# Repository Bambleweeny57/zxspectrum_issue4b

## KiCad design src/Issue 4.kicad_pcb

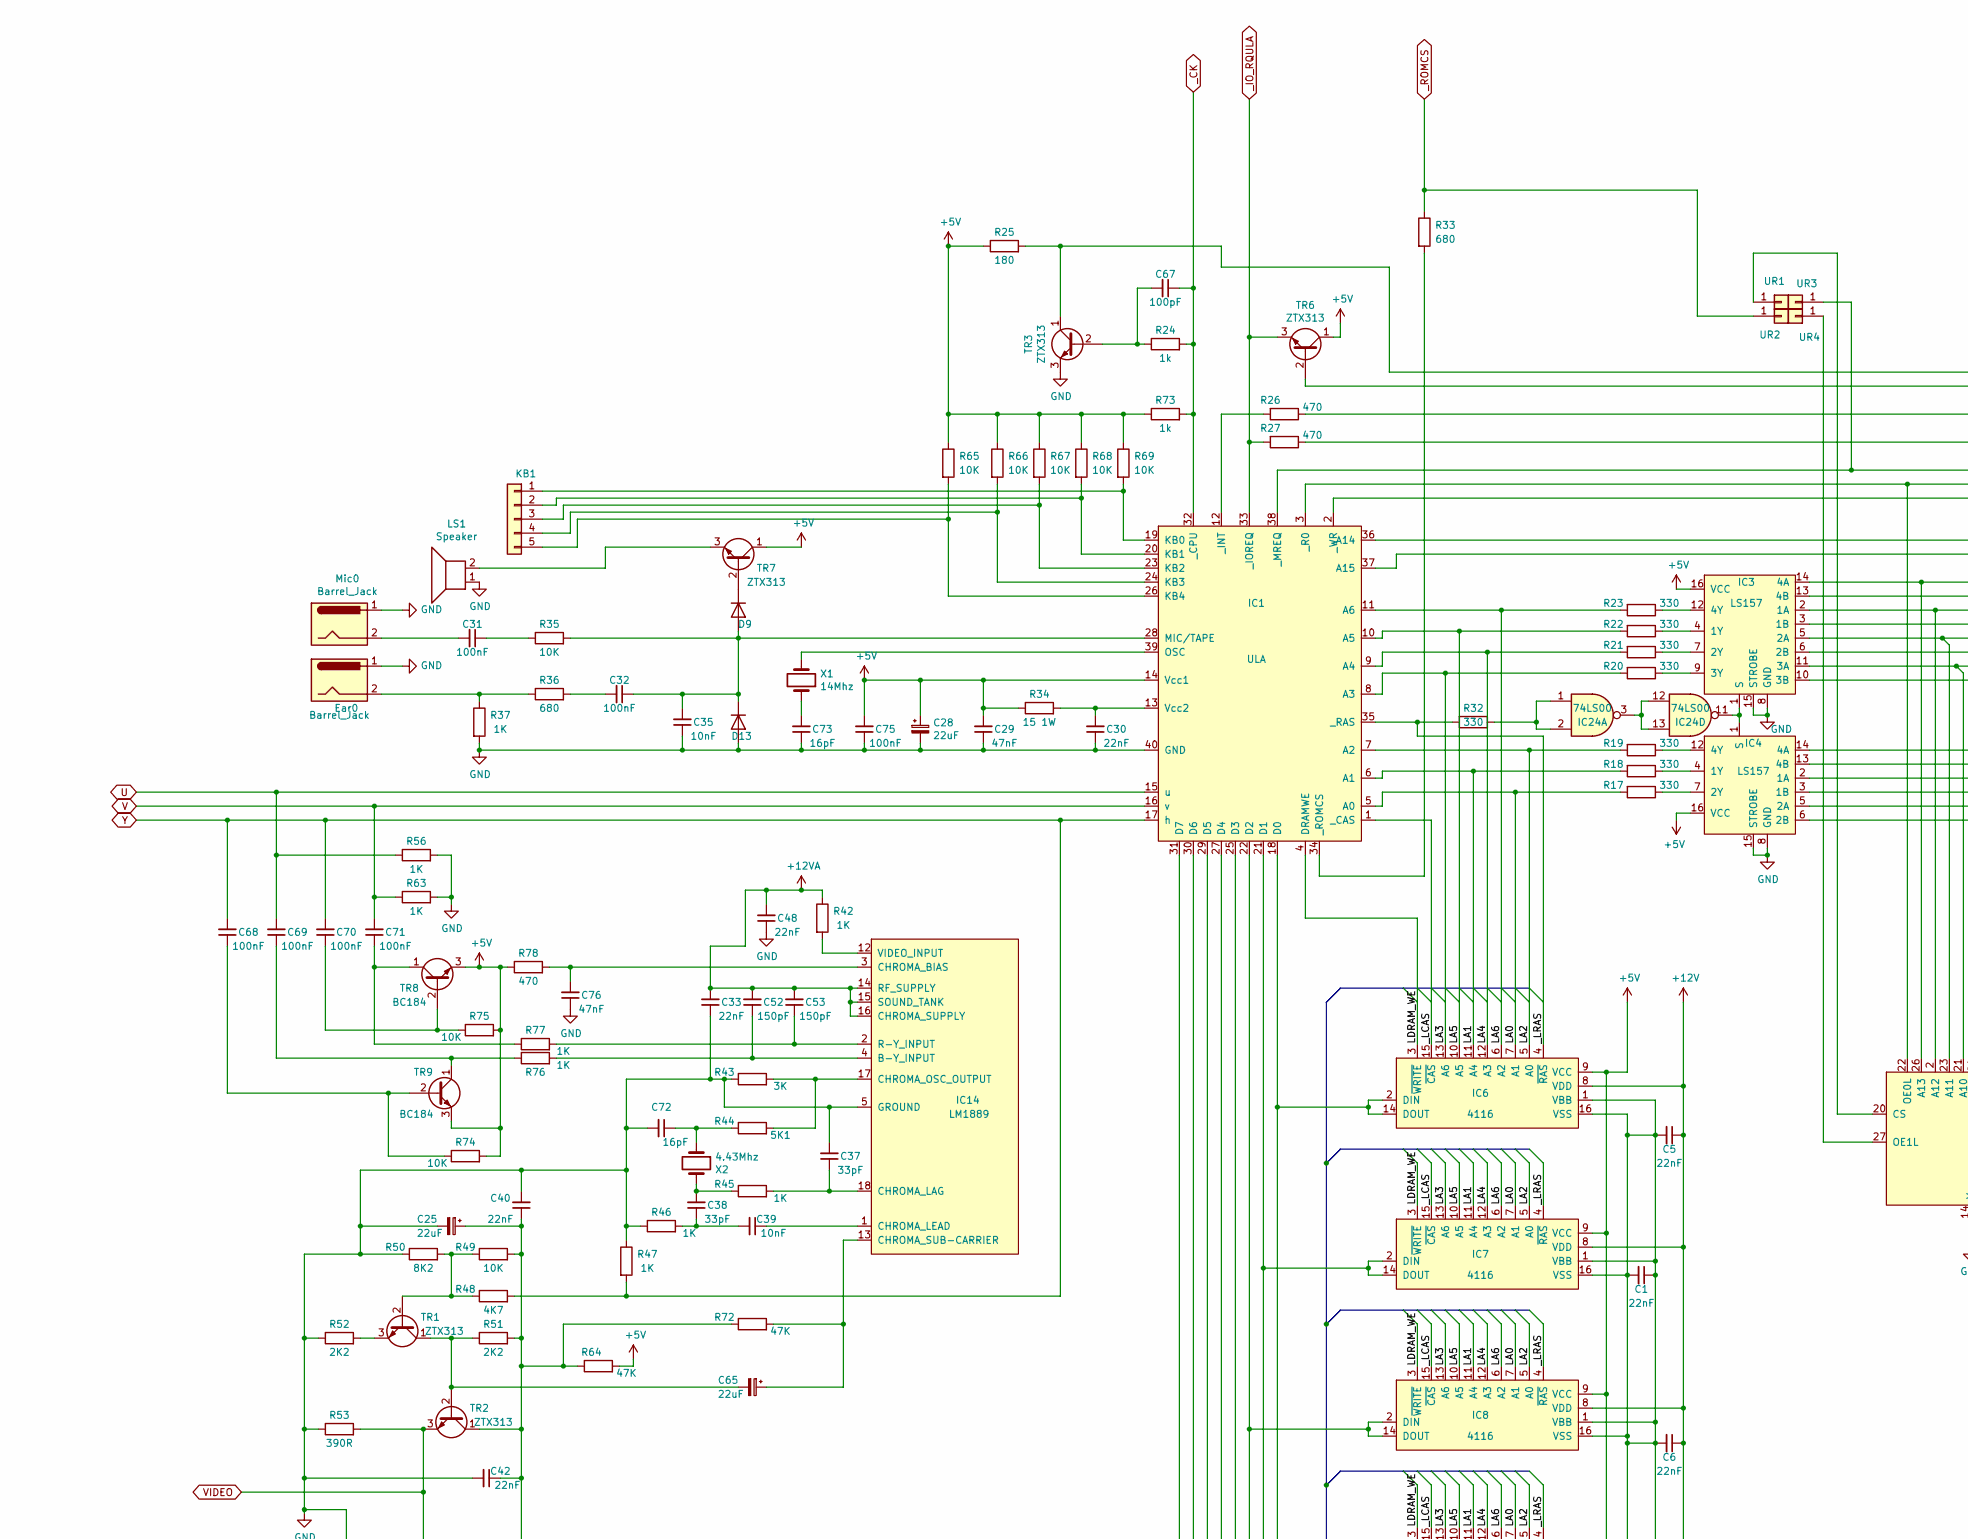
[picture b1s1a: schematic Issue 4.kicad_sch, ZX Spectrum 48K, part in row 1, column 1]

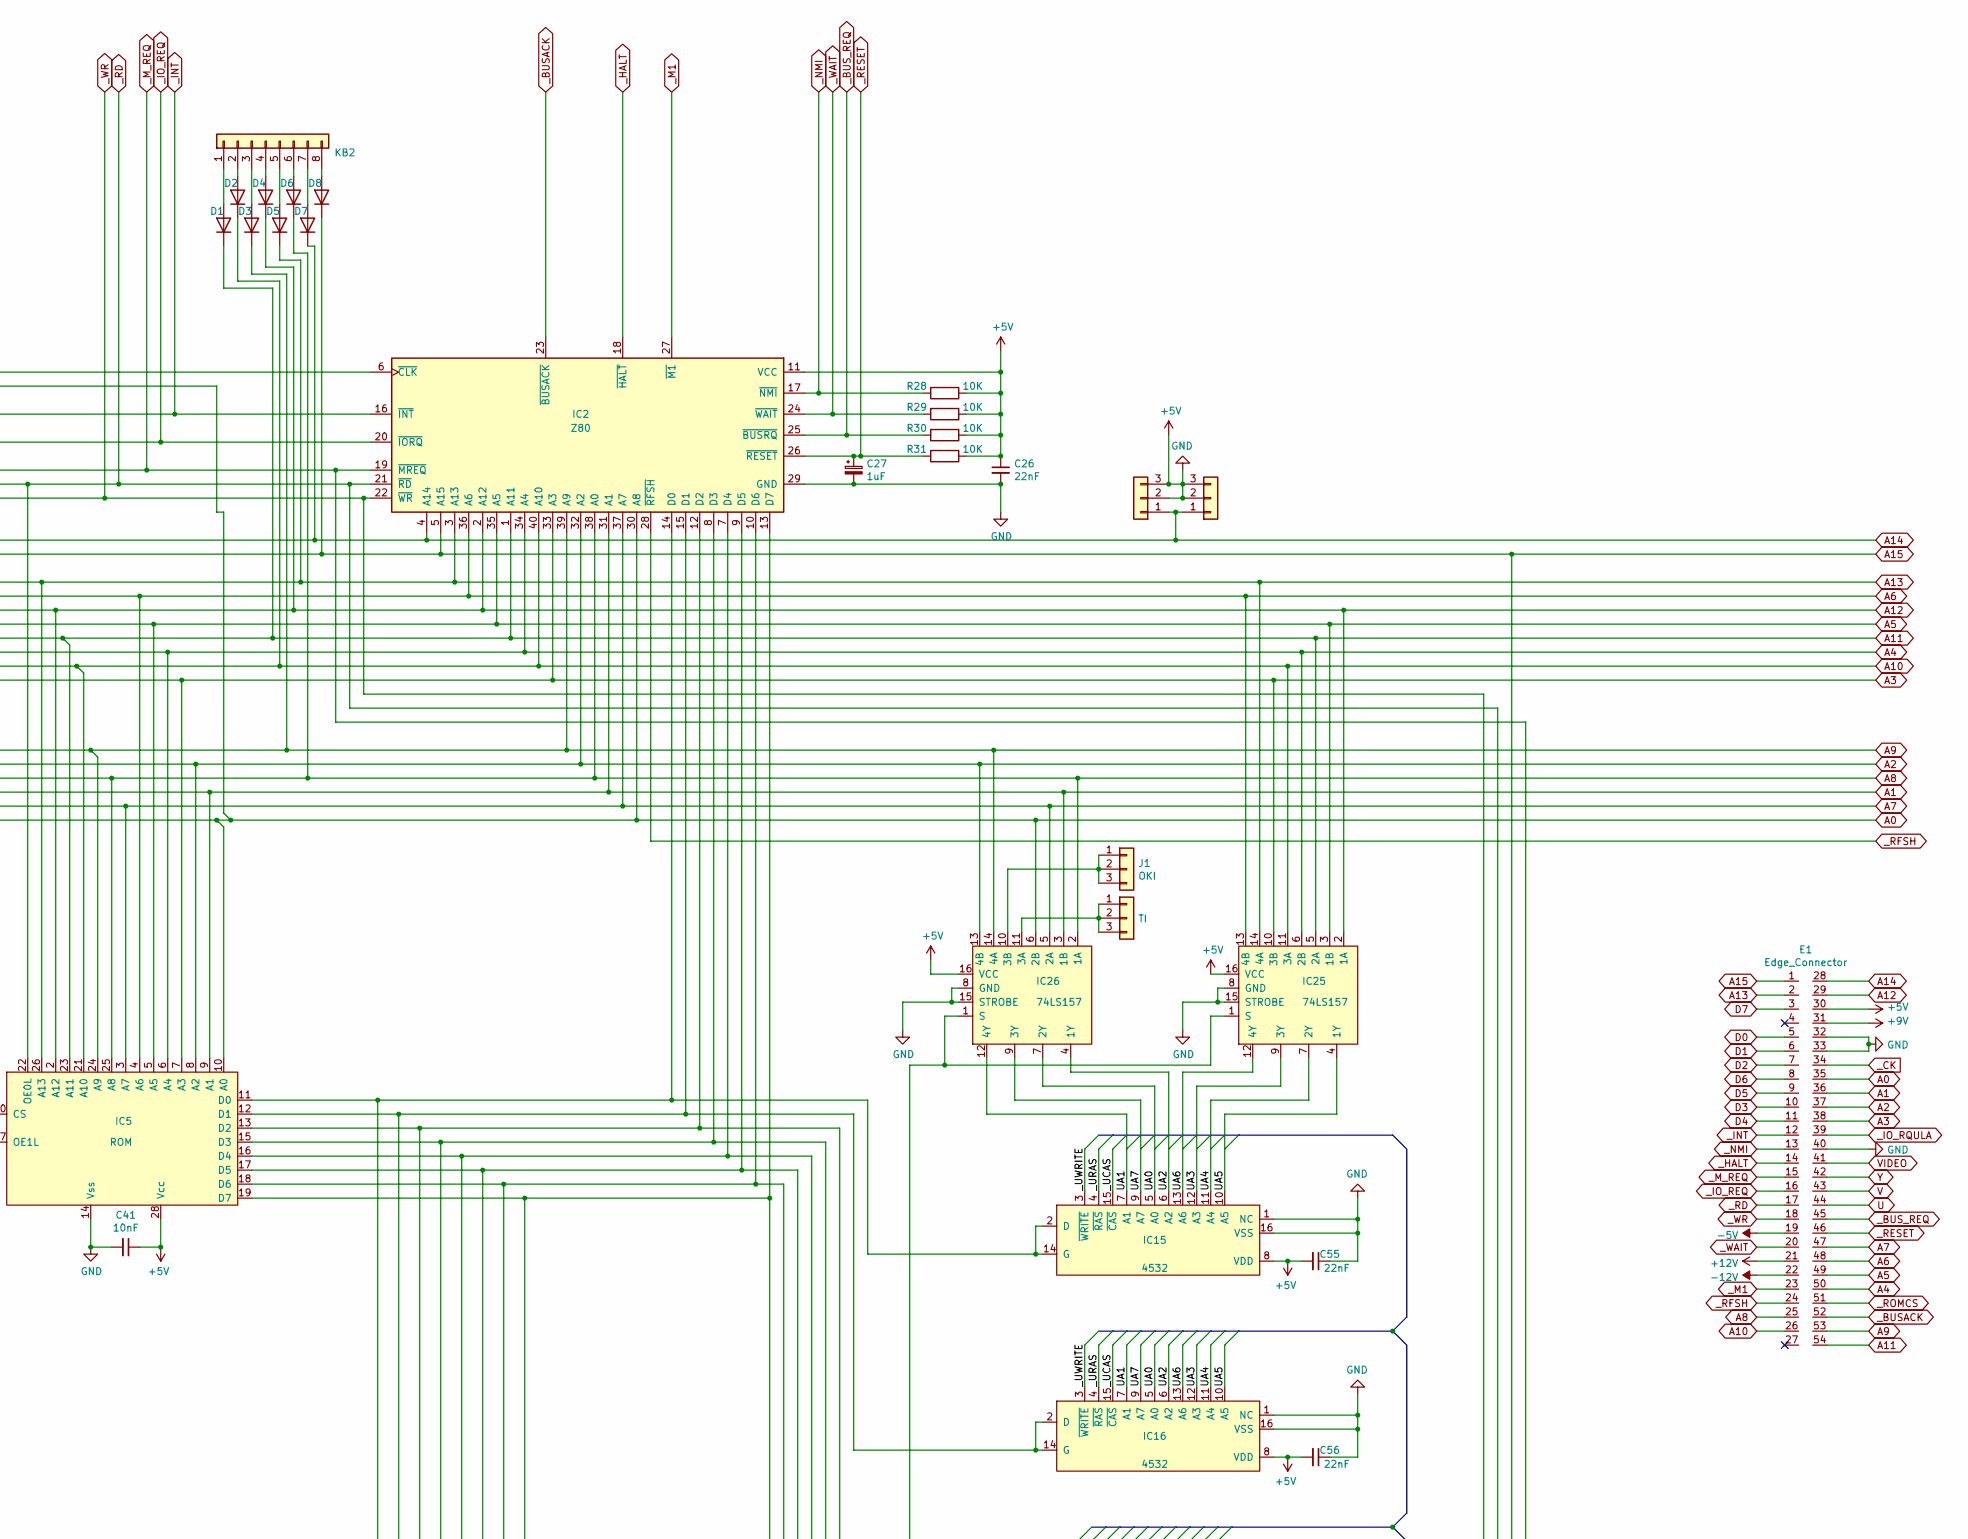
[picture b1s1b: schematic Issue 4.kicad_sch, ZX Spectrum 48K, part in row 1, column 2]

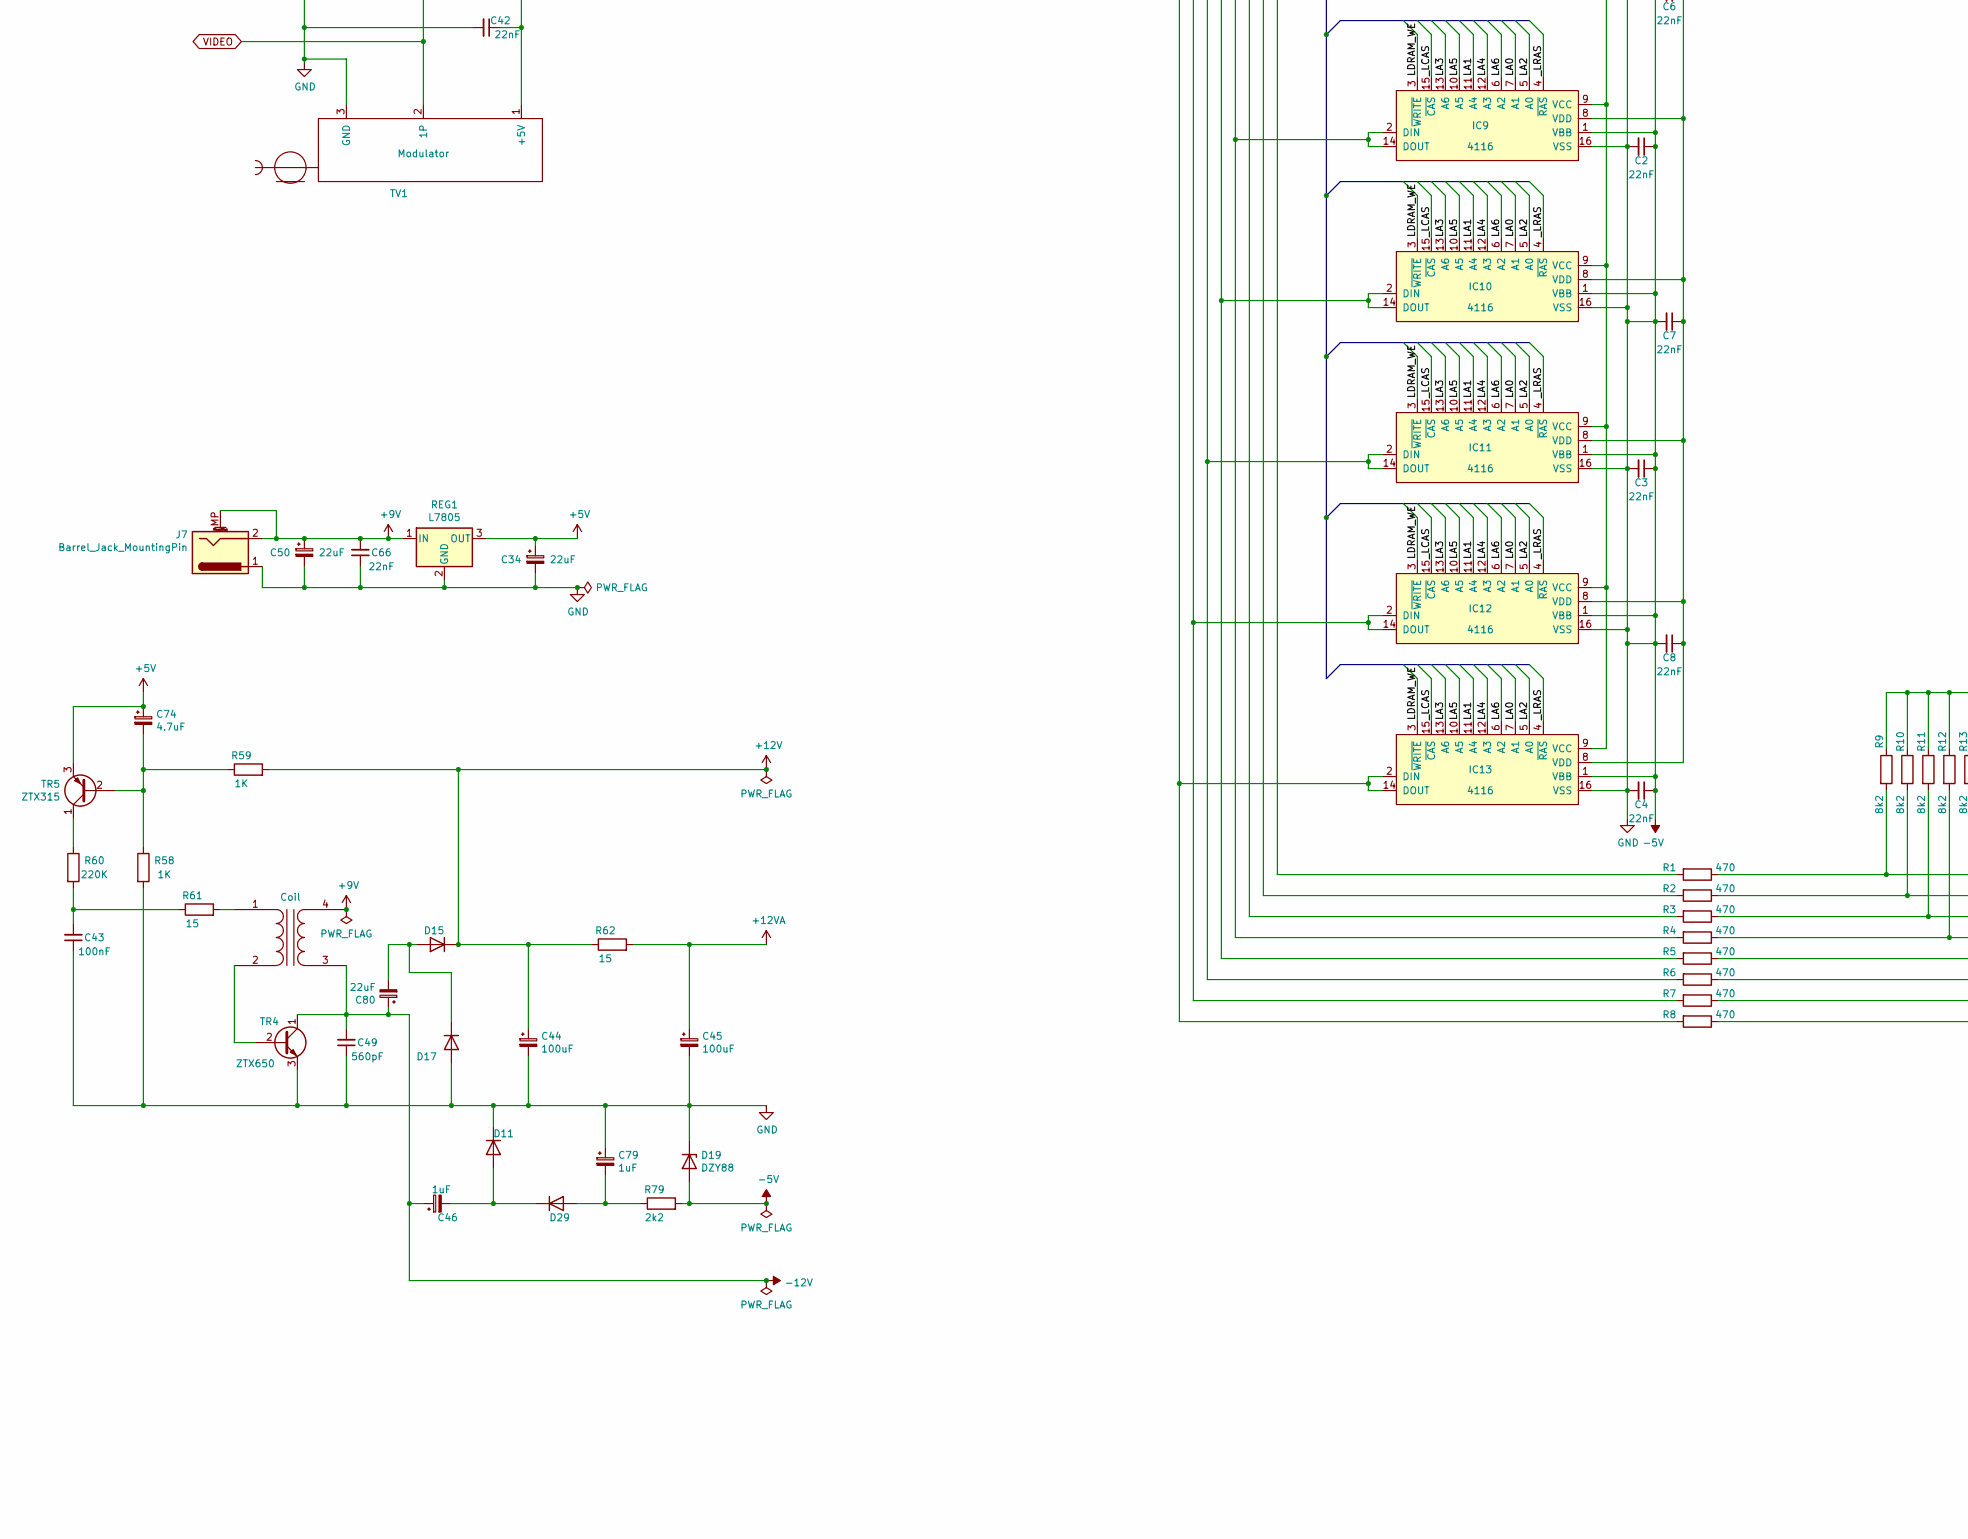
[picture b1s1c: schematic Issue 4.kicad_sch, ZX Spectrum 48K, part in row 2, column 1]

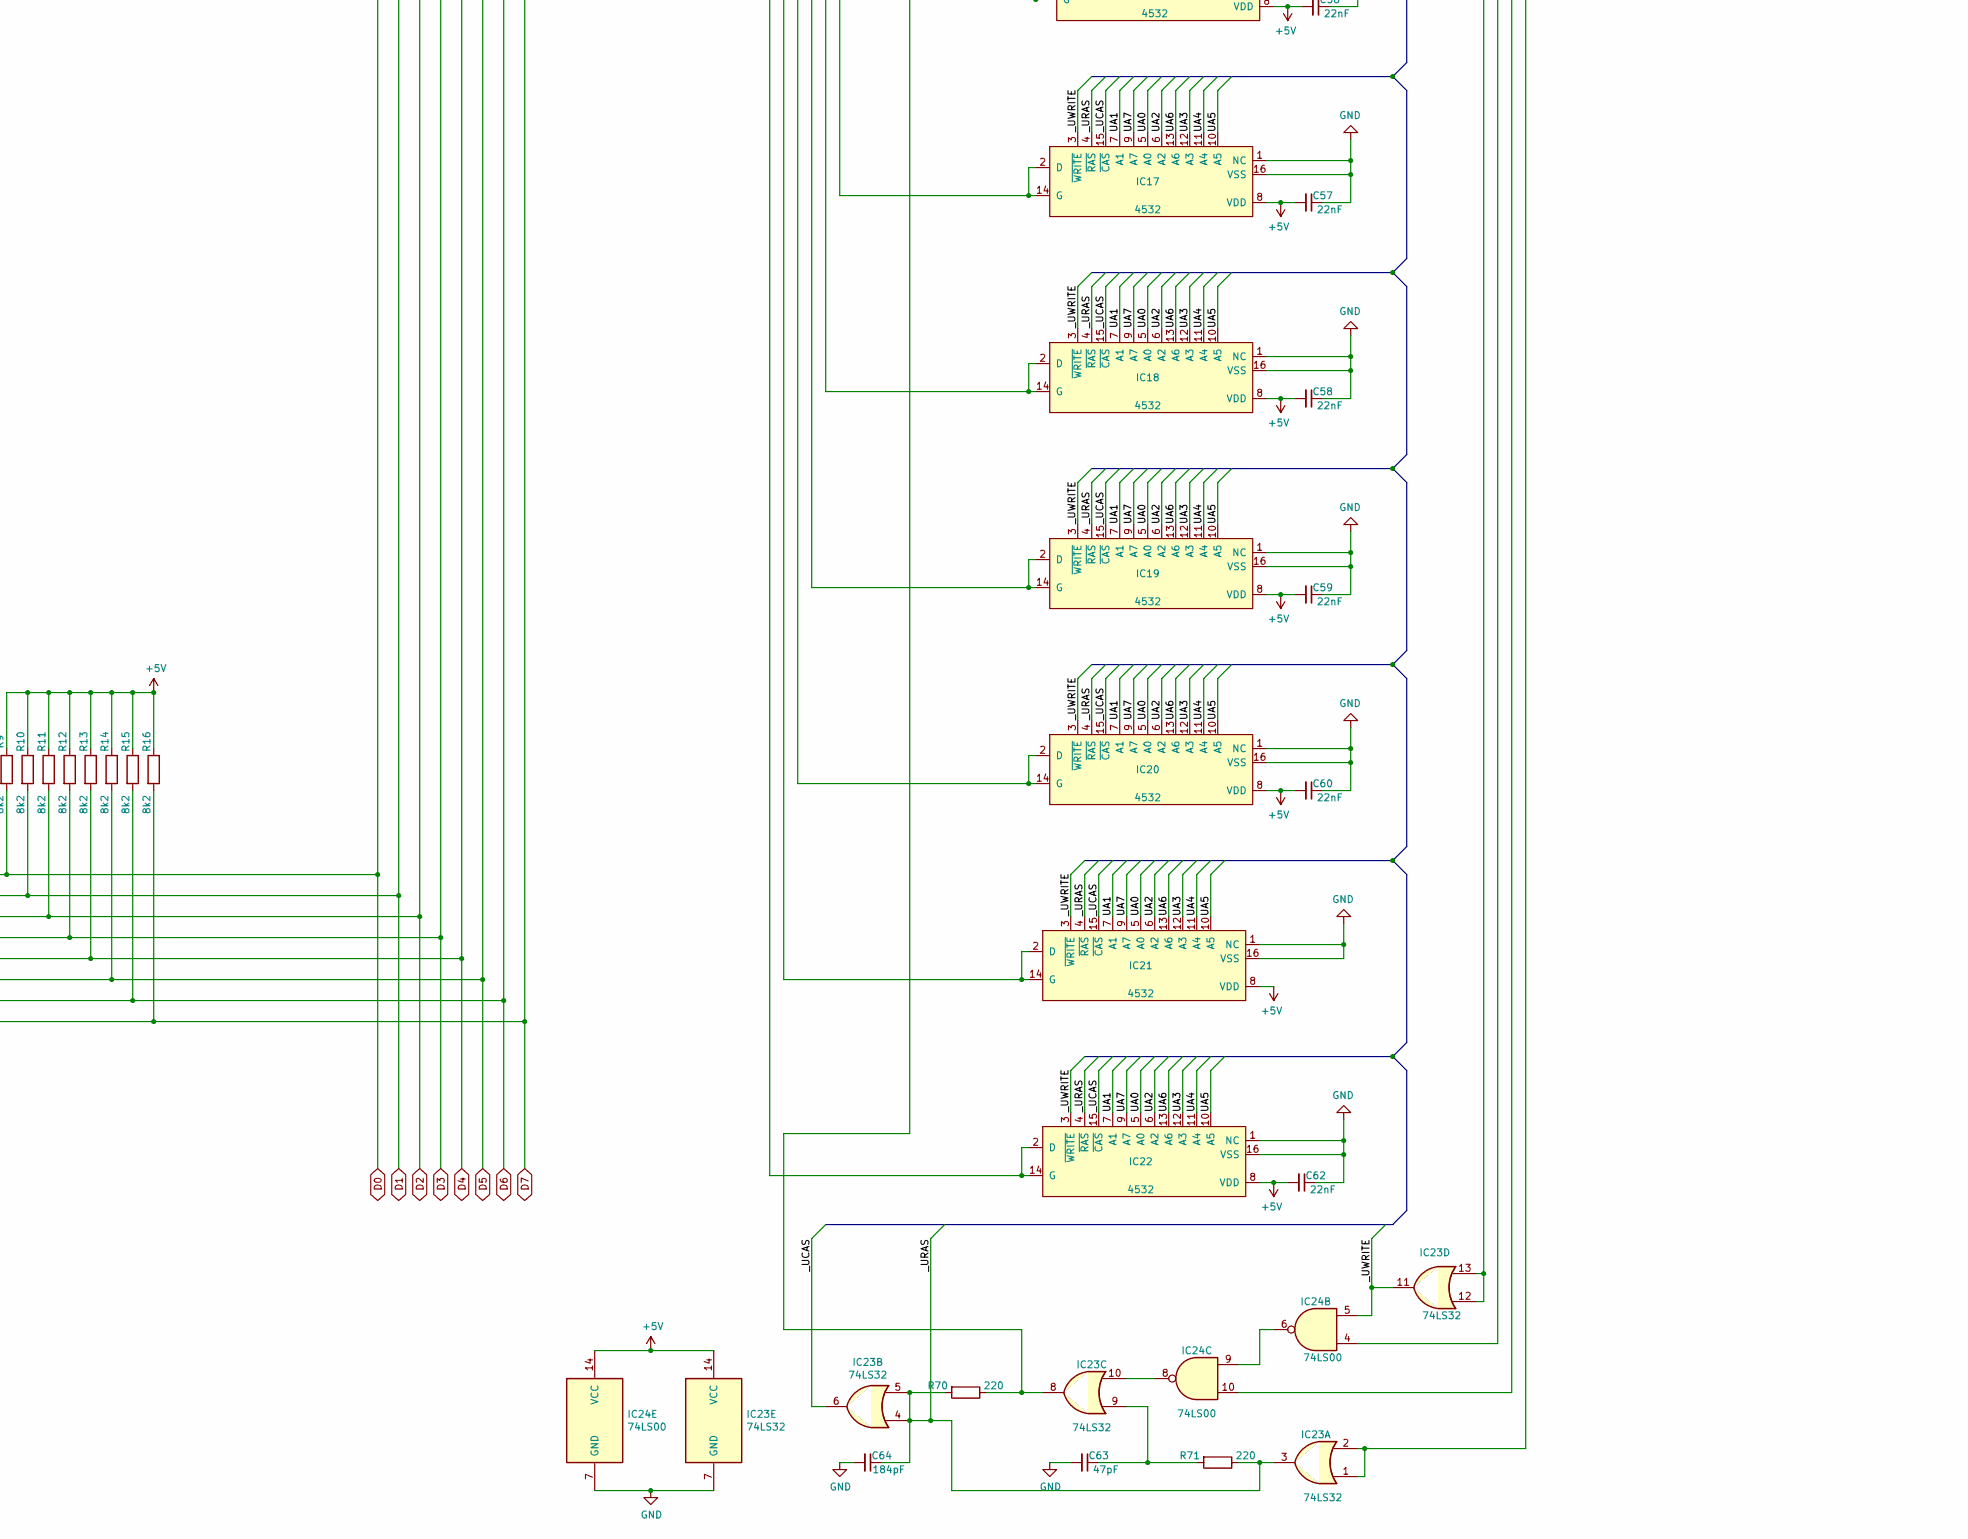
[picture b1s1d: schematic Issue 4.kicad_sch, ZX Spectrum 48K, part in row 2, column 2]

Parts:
C1, C2, C3, C4, C5, C6, C7, C8, C26, C30, C33, C40, C42, C48, C55, C56, C57, C58, C59, C60, C62, C66: 22nF; Passive_small
C25, C28, C34, C50, C65, C80: 22uF; CP_Axial_L11.0mm_D6.0mm_P18.00mm_Horizontal
C27, C46, C79: 1uF; CP_Axial_L11.0mm_D6.0mm_P18.00mm_Horizontal
C29, C76: 47nF; Passive_small
C31, C32, C43, C68, C69, C70, C71, C75: 100nF; Passive_small
C35, C39, C41: 10nF; Passive_small
C37, C38: 33pF; Passive_small
C44, C45: 100uF; CP_Axial_L11.0mm_D6.0mm_P18.00mm_Horizontal
C49: 560pF; Passive_small
C52, C53: 150pF; Passive_small
C63: 47pF; Passive_small
C64: 184pF; Passive_small
C67: 100pF; Passive_small
C72, C73: 16pF; Passive_small
C74: 4.7uF; CP_Axial_L11.0mm_D6.0mm_P18.00mm_Horizontal
D1, D2, D3, D4, D5, D6, D7, D8, D9, D11, D13, D15, D17, D29: 1N4148; Diode
D19: DZY88; D_DO-35_SOD27_P7.62mm_Horizontal
E1: Edge_Connector; Edge Connector
Ear0: Barrel_Jack; 3.5mm_socket
IC1: ULA; DIP-40_W15.24mm_Socket
IC2: Z80; DIP-40_W15.24mm_Socket
IC3, IC4: LS157; DIP-16_W7.62mm_Socket
IC5: ROM; DIP-28_W15.24mm_Socket
IC6, IC7, IC8, IC9, IC10, IC11, IC12, IC13: 4116; DIP-16_W7.62mm_Socket
IC14: LM1889; DIP-18_W7.62mm_Socket
IC15, IC16, IC17, IC18, IC19, IC20, IC21, IC22: 4532; DIP-16_W7.62mm_Socket
IC23: 74LS32; DIP-14_W7.62mm_Socket
IC24: 74LS00; DIP-14_W7.62mm_Socket
IC25, IC26: 74LS157; DIP-16_W7.62mm_Socket
J1: OKI; PinHeader_1x03_P2.54mm_Vertical
J2, J3, J4: TI; PinHeader_1x03_P2.54mm_Vertical
J7: Barrel_Jack_MountingPin; BarrelJack_Horizontal
J8: UR1; PinHeader_1x01_P2.54mm_Vertical
J9: UR2; PinHeader_1x01_P2.54mm_Vertical
J10: UR3; PinHeader_1x01_P2.54mm_Vertical
J11: UR4; PinHeader_1x01_P2.54mm_Vertical
KB1: Conn_01x05; PinSocket_1x05_P2.54mm_Vertical
KB2: Conn_01x08; PinSocket_1x08_P2.54mm_Vertical
LS1: Speaker
Mic0: Barrel_Jack; 3.5mm_socket
R1, R2, R3, R4, R5, R6, R7, R8, R26, R27, R78: 470; Passive_small
R9, R10, R11, R12, R13, R14, R15, R16: 8k2; Passive_small
R17, R18, R19, R20, R21, R22, R23, R32: 330; Passive_small
R24, R73: 1k; Passive_small
R25: 180; Passive_small
R28, R29, R30, R31, R35, R49, R65, R66, R67, R68, R69, R74, R75: 10K; Passive_small
R33, R36: 680; Passive_small
R34: 15 1W; R_Axial_Power_L20.0mm_W6.4mm_P22.40mm
R37, R42, R45, R46, R47, R56, R58, R59, R63, R76, R77: 1K; Passive_small
R43: 3K; Passive_small
R44: 5K1; Passive_small
R48: 4K7; Passive_small
R50: 8K2; Passive_small
R51, R52: 2K2; Passive_small
R53: 390R; Passive_small
R60: 220K; Passive_small
R61, R62: 15; Passive_small
R64, R72: 47K; Passive_small
R70, R71: 220; Passive_small
R79: 2k2; Passive_small
REG1: L7805; 3-SIP_Module_V7805-500
T1: Coil; Choke
TR1, TR2, TR3, TR6, TR7: ZTX313; TO-92Flat
TR4: ZTX650; TO-92Flat
TR5: ZTX315; TO-92Flat
TR8, TR9: BC184; TO-92_Inline
TV1: Modulator
X1: 14Mhz; Crystal_HC18-U_Vertical
X2: 4.43Mhz; Crystal_HC18-U_Horizontal

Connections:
+9V: C50.1, C66.2, E1.31, J7.2, J7.MP (MountPin), REG1.1 (IN), T1.4 (SB)
+12V: C5.1, C6.1, C7.1, C8.1, C44.1, D15.1 (K), E1.21, IC6.8 (VDD), IC7.8 (VDD), IC8.8 (VDD), IC9.8 (VDD), IC10.8 (VDD), IC11.8 (VDD), IC12.8 (VDD), IC13.8 (VDD), R59.2, R62.1
+12VA: C33.2, C45.1, C48.2, C52.2, C53.2, IC14.14 (RF_SUPPLY), IC14.15 (SOUND_TANK), IC14.16 (CHROMA_SUPPLY), R42.1, R62.2
-12V: C46.1, C49.2, C80.1, E1.22, T1.3 (SA), TR4.1 (C)
/LA0: IC1.5 (A0), IC6.7 (A1), IC7.7 (A1), IC8.7 (A1), IC9.7 (A1), IC10.7 (A1), IC11.7 (A1), IC12.7 (A1), IC13.7 (A1), R17.2
/LA1: IC1.6 (A1), IC6.11 (A4), IC7.11 (A4), IC8.11 (A4), IC9.11 (A4), IC10.11 (A4), IC11.11 (A4), IC12.11 (A4), IC13.11 (A4), R18.2
/LA2: IC1.7 (A2), IC6.5 (A0), IC7.5 (A0), IC8.5 (A0), IC9.5 (A0), IC10.5 (A0), IC11.5 (A0), IC12.5 (A0), IC13.5 (A0), R19.2
/LA3: IC1.8 (A3), IC6.13 (A6), IC7.13 (A6), IC8.13 (A6), IC9.13 (A6), IC10.13 (A6), IC11.13 (A6), IC12.13 (A6), IC13.13 (A6), R20.2
/LA4: IC1.9 (A4), IC6.12 (A3), IC7.12 (A3), IC8.12 (A3), IC9.12 (A3), IC10.12 (A3), IC11.12 (A3), IC12.12 (A3), IC13.12 (A3), R21.2
/LA5: IC1.10 (A5), IC6.10 (A5), IC7.10 (A5), IC8.10 (A5), IC9.10 (A5), IC10.10 (A5), IC11.10 (A5), IC12.10 (A5), IC13.10 (A5), R22.2
/LA6: IC1.11 (A6), IC6.6 (A2), IC7.6 (A2), IC8.6 (A2), IC9.6 (A2), IC10.6 (A2), IC11.6 (A2), IC12.6 (A2), IC13.6 (A2), R23.2
/LDRAM_WE: IC1.4 (DRAMWE), IC6.3 (~WRITE), IC7.3 (~WRITE), IC8.3 (~WRITE), IC9.3 (~WRITE), IC10.3 (~WRITE), IC11.3 (~WRITE), IC12.3 (~WRITE), IC13.3 (~WRITE)
/UA0: IC15.5 (A0), IC16.5 (A0), IC17.5 (A0), IC18.5 (A0), IC19.5 (A0), IC20.5 (A0), IC21.5 (A0), IC22.5 (A0), IC26.7 (2Y)
/UA1: IC15.7 (A1), IC16.7 (A1), IC17.7 (A1), IC18.7 (A1), IC19.7 (A1), IC20.7 (A1), IC21.7 (A1), IC22.7 (A1), IC26.12 (4Y)
/UA2: IC15.6 (A2), IC16.6 (A2), IC17.6 (A2), IC18.6 (A2), IC19.6 (A2), IC20.6 (A2), IC21.6 (A2), IC22.6 (A2), IC26.4 (1Y)
/UA3: IC15.12 (A3), IC16.12 (A3), IC17.12 (A3), IC18.12 (A3), IC19.12 (A3), IC20.12 (A3), IC21.12 (A3), IC22.12 (A3), IC25.9 (3Y)
/UA4: IC15.11 (A4), IC16.11 (A4), IC17.11 (A4), IC18.11 (A4), IC19.11 (A4), IC20.11 (A4), IC21.11 (A4), IC22.11 (A4), IC25.7 (2Y)
/UA5: IC15.10 (A5), IC16.10 (A5), IC17.10 (A5), IC18.10 (A5), IC19.10 (A5), IC20.10 (A5), IC21.10 (A5), IC22.10 (A5), IC25.4 (1Y)
/UA6: IC15.13 (A6), IC16.13 (A6), IC17.13 (A6), IC18.13 (A6), IC19.13 (A6), IC20.13 (A6), IC21.13 (A6), IC22.13 (A6), IC25.12 (4Y)
/UA7: IC15.9 (A7), IC16.9 (A7), IC17.9 (A7), IC18.9 (A7), IC19.9 (A7), IC20.9 (A7), IC21.9 (A7), IC22.9 (A7), IC26.9 (3Y)
/_LCAS: IC1.1 (_CAS), IC6.15 (~CAS), IC7.15 (~CAS), IC8.15 (~CAS), IC9.15 (~CAS), IC10.15 (~CAS), IC11.15 (~CAS), IC12.15 (~CAS), IC13.15 (~CAS)
/_LRAS: IC1.35 (_RAS), IC6.4 (~RAS), IC7.4 (~RAS), IC8.4 (~RAS), IC9.4 (~RAS), IC10.4 (~RAS), IC11.4 (~RAS), IC12.4 (~RAS), IC13.4 (~RAS), R32.2
/_UCAS: IC15.15 (~CAS), IC16.15 (~CAS), IC17.15 (~CAS), IC18.15 (~CAS), IC19.15 (~CAS), IC20.15 (~CAS), IC21.15 (~CAS), IC22.15 (~CAS), IC23.6
/_UWRITE: IC15.3 (~WRITE), IC16.3 (~WRITE), IC17.3 (~WRITE), IC18.3 (~WRITE), IC19.3 (~WRITE), IC20.3 (~WRITE), IC21.3 (~WRITE), IC22.3 (~WRITE), IC23.11, IC24.5
A0: E1.35, IC2.30 (A8), IC4.6 (2B), IC5.10 (A0), IC26.6 (2B), TR6.2 (B)
A1: E1.36, IC2.31 (A1), IC4.3 (1B), IC5.9 (A1), IC26.3 (1B)
A2: E1.37, IC2.32 (A2), IC4.13 (4B), IC5.8 (A2), IC26.13 (4B)
A3: E1.38, IC2.33 (A3), IC3.10 (3B), IC5.7 (A3), IC25.10 (3B)
A4: E1.50, IC2.34 (A4), IC3.6 (2B), IC5.6 (A4), IC25.6 (2B)
A5: E1.49, IC2.35 (A5), IC3.3 (1B), IC5.5 (A5), IC25.3 (1B)
A6: E1.48, IC2.36 (A6), IC3.13 (4B), IC5.4 (A6), IC25.13 (4B)
A7: E1.47, IC2.37 (A7), IC4.5 (2A), IC5.3 (A7), IC26.5 (2A)
A8: D6.1 (K), E1.25, IC2.38 (A0), IC4.2 (1A), IC5.25 (A8), IC26.2 (1A)
A9: D3.1 (K), E1.53, IC2.39 (A9), IC4.14 (4A), IC5.24 (A9), IC26.14 (4A)
A10: D2.1 (K), E1.26, IC2.40 (A10), IC3.11 (3A), IC5.21 (A10), IC25.11 (3A)
A11: D1.1 (K), E1.54, IC2.1 (A11), IC3.5 (2A), IC5.23 (A11), IC25.5 (2A)
A12: D4.1 (K), E1.29, IC2.2 (A12), IC3.2 (1A), IC5.2 (A12), IC25.2 (1A)
A13: D5.1 (K), E1.2, IC2.3 (A13), IC3.14 (4A), IC5.26 (A13), IC25.14 (4A)
A14: D7.1 (K), E1.28, IC1.36 (A14), IC2.4 (A14), J3.1, J4.1
A15: D8.1 (K), E1.1, IC1.37 (A15), IC2.5 (A15), IC24.10
D0: E1.5, IC2.14 (D0), IC5.11 (D0), IC15.2 (D), IC15.14 (G), R1.1, R9.2
D1: E1.6, IC2.15 (D1), IC5.12 (D1), IC16.2 (D), IC16.14 (G), R2.1, R10.2
D2: E1.7, IC2.12 (D2), IC5.13 (D2), IC17.2 (D), IC17.14 (G), R3.1, R11.2
D3: E1.10, IC2.8 (D3), IC5.15 (D3), IC18.2 (D), IC18.14 (G), R4.1, R12.2
D4: E1.11, IC2.7 (D4), IC5.16 (D4), IC19.2 (D), IC19.14 (G), R5.1, R13.2
D5: E1.9, IC2.9 (D5), IC5.17 (D5), IC20.2 (D), IC20.14 (G), R6.1, R14.2
D6: E1.8, IC2.10 (D6), IC5.18 (D6), IC21.2 (D), IC21.14 (G), R7.1, R15.2
D7: E1.3, IC2.13 (D7), IC5.19 (D7), IC22.2 (D), IC22.14 (G), R8.1, R16.2
unnamed: C25.1, C40.1, C42.1, R49.2, R51.2, R64.1, R72.1, TR2.1 (C), TV1.1 (+5V)
unnamed: C30.2, IC1.13 (Vcc2), R34.2
unnamed: C31.1, R35.1
unnamed: C31.2, Mic0.2
unnamed: C32.1, C35.2, D9.2 (A), D13.1 (K), IC1.28 (MIC/TAPE), R35.2
unnamed: C32.2, R36.2
unnamed: C37.1, IC14.18 (CHROMA_LAG), R45.2
unnamed: C38.1, C39.2, R46.2
unnamed: C38.2, R45.1, X2.2
unnamed: C39.1, IC14.1 (CHROMA_LEAD)
unnamed: C43.2, R60.2, R61.1
unnamed: C46.2, D11.2 (A), D29.1 (K)
unnamed: C52.1, IC14.4 (B-Y_INPUT), R76.2
unnamed: C53.1, IC14.2 (R-Y_INPUT), R77.2
unnamed: C63.1, IC23.9, R71.2
unnamed: C65.1, IC14.13 (CHROMA_SUB-CARRIER), R72.2
unnamed: C65.2, R51.1, TR1.1 (C), TR2.2 (B)
unnamed: C67.2, R24.1, TR3.2 (B)
unnamed: C68.1, R74.1, TR9.2 (B)
unnamed: C69.1, R76.1, TR9.1 (C)
unnamed: C70.1, R75.1, TR8.2 (B)
unnamed: C71.1, R77.1, TR8.1 (C)
unnamed: C72.1, R44.1, X2.1
unnamed: C73.2, X1.1
unnamed: C74.2, R58.1, R59.1, TR5.2 (B)
unnamed: C76.2, IC14.3 (CHROMA_BIAS), R78.2
unnamed: C79.2, D29.2 (A), R79.1
unnamed: C80.2, D15.2 (A), D17.1 (K)
unnamed: D1.2 (A), KB2.1
unnamed: D2.2 (A), KB2.2
unnamed: D3.2 (A), KB2.3
unnamed: D4.2 (A), KB2.4
unnamed: D5.2 (A), KB2.5
unnamed: D6.2 (A), KB2.6
unnamed: D7.2 (A), KB2.7
unnamed: D8.2 (A), KB2.8
unnamed: D9.1 (K), TR7.2 (B)
unnamed: Ear0.2, R36.1, R37.1
unnamed: IC1.12 (_INT), R26.2
unnamed: IC1.18 (D0), IC6.2 (DIN), IC6.14 (DOUT), R1.2
unnamed: IC1.19 (KB0), KB1.1, R69.2
unnamed: IC1.20 (KB1), KB1.2, R68.2
unnamed: IC1.21 (D1), IC7.2 (DIN), IC7.14 (DOUT), R2.2
unnamed: IC1.22 (D2), IC8.2 (DIN), IC8.14 (DOUT), R3.2
unnamed: IC1.23 (KB2), KB1.3, R67.2
unnamed: IC1.24 (KB3), KB1.4, R66.2
unnamed: IC1.25 (D3), IC9.2 (DIN), IC9.14 (DOUT), R4.2
unnamed: IC1.26 (KB4), KB1.5, R65.2
unnamed: IC1.27 (D4), IC10.2 (DIN), IC10.14 (DOUT), R5.2
unnamed: IC1.29 (D5), IC11.2 (DIN), IC11.14 (DOUT), R6.2
unnamed: IC1.30 (D6), IC12.2 (DIN), IC12.14 (DOUT), R7.2
unnamed: IC1.31 (D7), IC13.2 (DIN), IC13.14 (DOUT), R8.2
unnamed: IC1.34 (_ROMCS), R33.2
unnamed: IC1.39 (OSC), X1.2
unnamed: IC2.6 (~CLK), R25.2, TR3.1 (C)
unnamed: IC3.4 (1Y), R22.1
unnamed: IC3.7 (2Y), R21.1
unnamed: IC3.9 (3Y), R20.1
unnamed: IC3.12 (4Y), R23.1
unnamed: IC4.4 (1Y), R18.1
unnamed: IC4.7 (2Y), R17.1
unnamed: IC4.12 (4Y), R19.1
unnamed: IC5.20 (CS), J8.1
unnamed: IC5.27 (OE1L), J11.1
unnamed: IC14.12 (VIDEO_INPUT), R42.2
unnamed: IC14.17 (CHROMA_OSC_OUTPUT), R43.2, R44.2
unnamed: IC23.8, IC25.1 (S), IC26.1 (S), R70.1
unnamed: IC23.10, IC24.8
unnamed: IC24.1, IC24.2, R32.1
unnamed: IC24.6, IC24.9
unnamed: IC3.1 (S), IC4.1 (S), IC24.11
unnamed: IC24.3, IC24.12, IC24.13
unnamed: IC26.10 (3B), J1.1, J1.2, J1.3
unnamed: IC26.11 (3A), J2.1, J2.2, J2.3
unnamed: LS1.2, TR7.3 (E)
unnamed: R48.1, R49.1, R50.2, TR1.2 (B)
unnamed: R52.2, TR1.3 (E)
unnamed: R60.1, TR5.1 (C)
unnamed: R61.2, T1.1 (AA)
unnamed: T1.2 (AB), TR4.2 (B)
U: C69.2, E1.44, IC1.15 (u), R56.1
V: C71.2, E1.43, IC1.16 (v), R63.1
VIDEO: E1.41, R53.2, TR2.3 (E), TV1.2 (1P)
Y: C68.2, C70.2, E1.42, IC1.17 (h), R47.2, R48.2
_BUSACK: E1.52, IC2.23 (~BUSACK)
_BUS_REQ: E1.45, IC2.25 (~BUSRQ), R30.2
_CK: C67.1, E1.34, IC1.32 (_CPU), R24.2, R73.2
_HALT: E1.14, IC2.18 (~HALT)
_INT: E1.12, IC2.16 (~INT), R26.1
_IO_REQ: E1.16, IC2.20 (~IORQ), R27.1
_IO_RQULA: E1.39, IC1.33 (_IOREQ), R27.2, TR6.3 (E)
_M1: E1.23, IC2.27 (~M1)
_M_REQ: E1.15, IC1.38 (_MREQ), IC2.19 (~MREQ), IC23.1, IC23.2, J10.1
_NMI: E1.13, IC2.17 (~NMI), R28.2
_RD: E1.17, IC1.3 (_R0), IC2.21 (~RD), IC5.22 (OE0L), IC24.4
_RESET: C27.1, E1.46, IC2.26 (~RESET), R31.2
_RFSH: E1.24, IC2.28 (~RFSH)
_ROMCS: E1.51, J9.1, R33.1
_WAIT: E1.20, IC2.24 (~WAIT), R29.2
_WR: E1.18, IC1.2 (_WR), IC2.22 (~WR), IC23.12, IC23.13

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
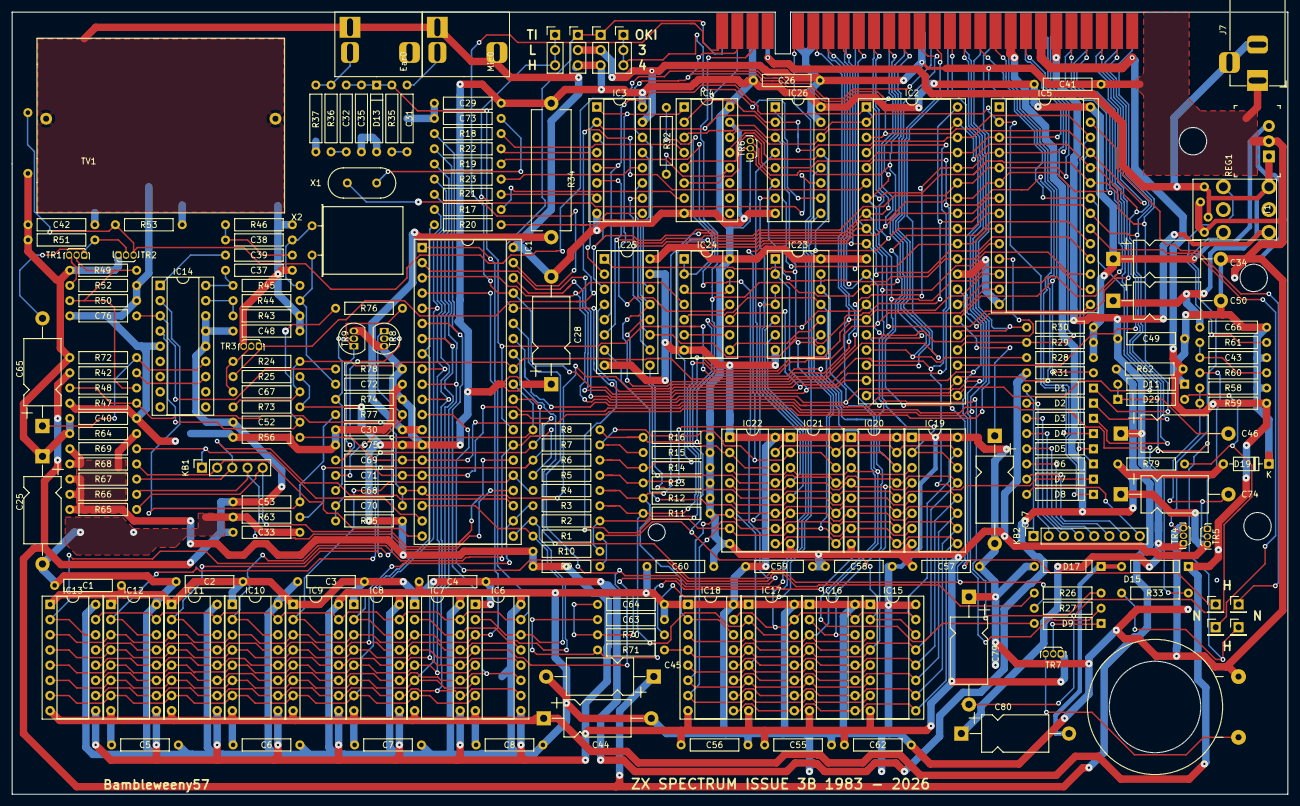
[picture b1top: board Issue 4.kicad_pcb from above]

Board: 2 copper layers, 213.4 x 130.8 mm, 199 parts (0 on the bottom side), 153 nets.

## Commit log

2025-09-28 initial push
2025-09-28 moved to src
2025-11-04 created pcb for coil
2025-11-09 3d model of the coil
2025-11-09 2 3d images
2025-11-10 pcb fab files for coil
2025-12-22 created ibom
2025-12-22 added pcb title
2026-01-19 re routed ear and mic and coil
